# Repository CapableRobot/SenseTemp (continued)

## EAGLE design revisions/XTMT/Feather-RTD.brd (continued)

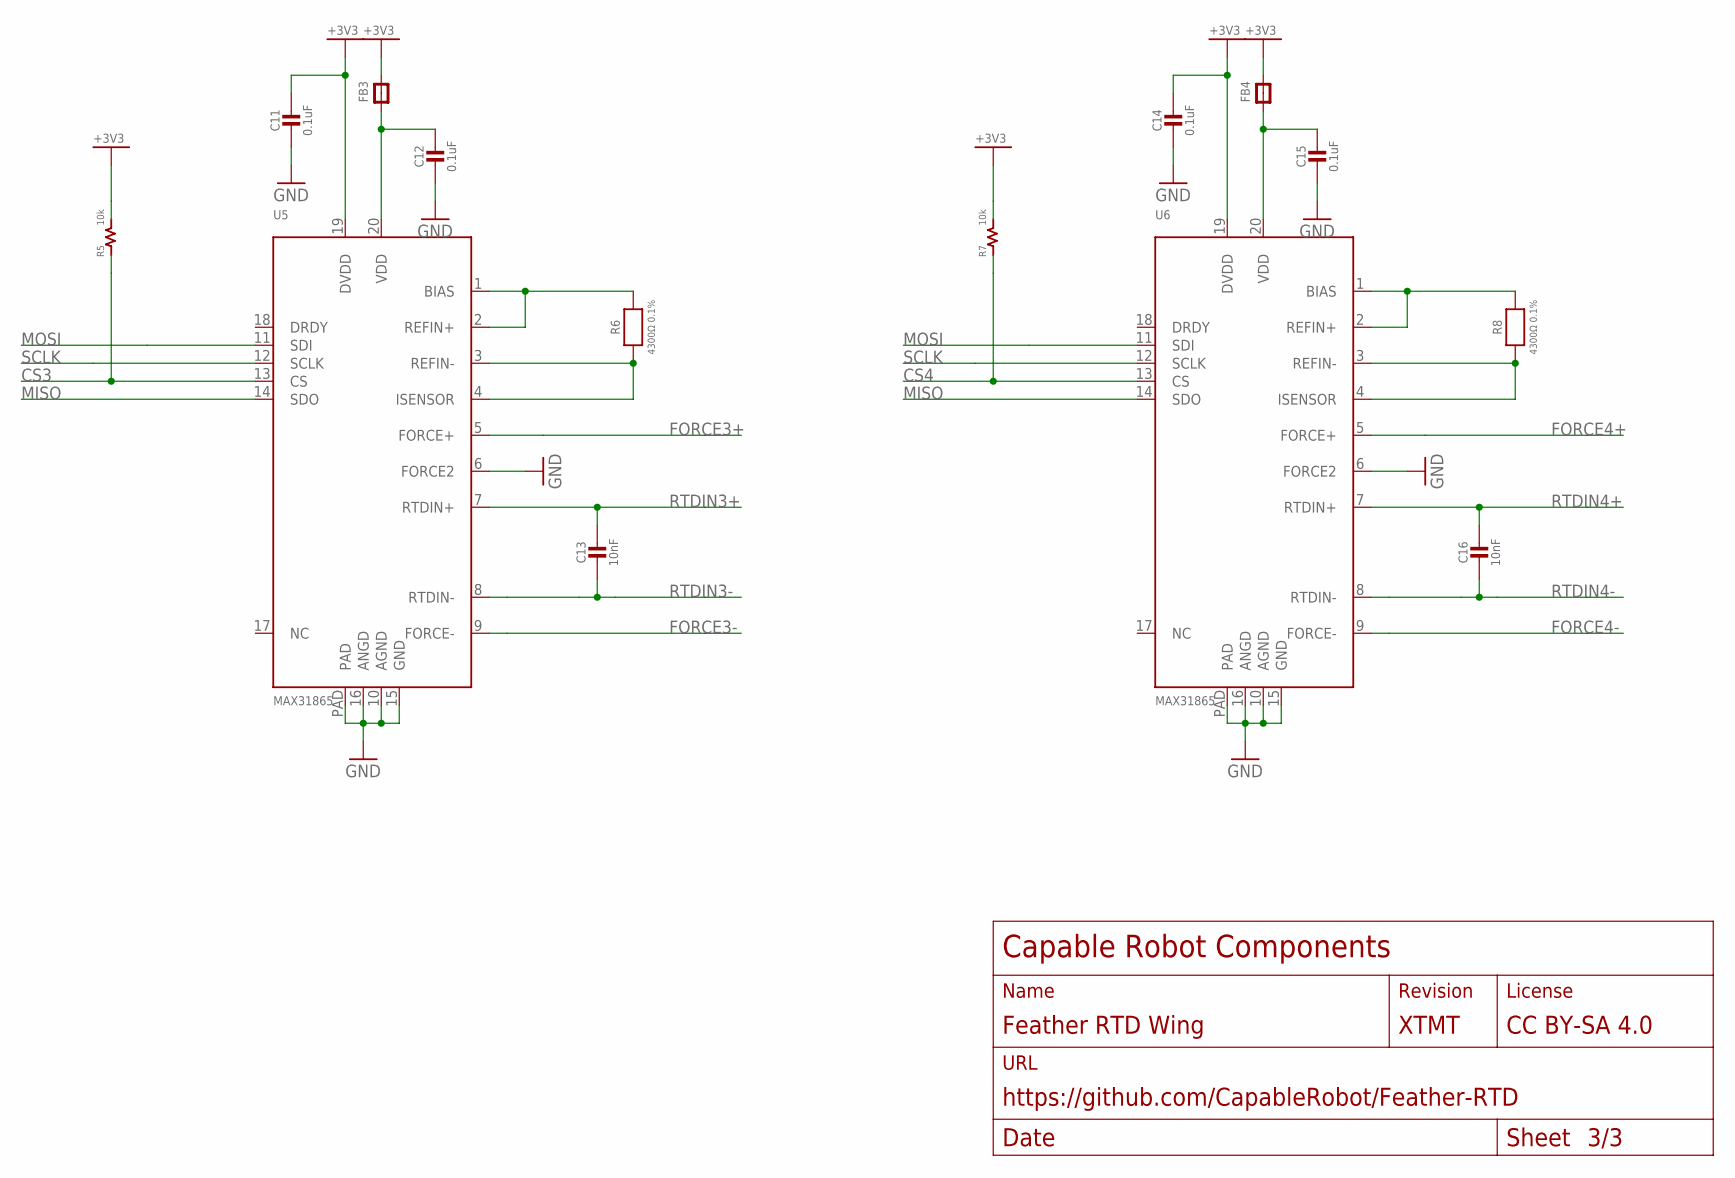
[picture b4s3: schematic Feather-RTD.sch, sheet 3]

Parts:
C11, C12, C14, C15: 0.1uF; 0805-NO
C13, C16: 10nF; 0805-NO
FB3, FB4: FERRITE-0805NO; 0805-NO
R5, R7: 10k; 0603
R6, R8: 4300Ω 0.1%; 0805-NO
U5, U6: MAX31865; QFN20_4MM_0.65MM

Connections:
+3V3: C11.1, C14.1, FB3.2, FB4.2, R5.2, R7.2, U5.19 (DVDD), U6.19 (DVDD); also elsewhere on the board
CS3: R5.1, U5.13 (CS); also elsewhere on the board
CS4: R7.1, U6.13 (CS); also elsewhere on the board
FORCE3+: U5.5 (FORCE+); also elsewhere on the board
FORCE3-: U5.9 (FORCE-); also elsewhere on the board
FORCE4+: U6.5 (FORCE+); also elsewhere on the board
FORCE4-: U6.9 (FORCE-); also elsewhere on the board
GND: C11.2, C12.2, C14.2, C15.2, U5.6 (FORCE2), U5.10 (AGND), U5.15 (GND), U5.16 (ANGD), U5.PAD, U6.6 (FORCE2), U6.10 (AGND), U6.15 (GND), U6.16 (ANGD), U6.PAD; also elsewhere on the board
MISO: U5.14 (SDO), U6.14 (SDO); also elsewhere on the board
MOSI: U5.11 (SDI), U6.11 (SDI); also elsewhere on the board
unnamed: R6.2, U5.1 (BIAS), U5.2 (REFIN+)
unnamed: R6.1, U5.3 (REFIN-), U5.4 (ISENSOR)
unnamed: C12.1, FB3.1, U5.20 (VDD)
unnamed: R8.2, U6.1 (BIAS), U6.2 (REFIN+)
unnamed: R8.1, U6.3 (REFIN-), U6.4 (ISENSOR)
unnamed: C15.1, FB4.1, U6.20 (VDD)
RTDIN3+: C13.1, U5.7 (RTDIN+); also elsewhere on the board
RTDIN3-: C13.2, U5.8 (RTDIN-); also elsewhere on the board
RTDIN4+: C16.1, U6.7 (RTDIN+); also elsewhere on the board
RTDIN4-: C16.2, U6.8 (RTDIN-); also elsewhere on the board
SCLK: U5.12 (SCLK), U6.12 (SCLK); also elsewhere on the board

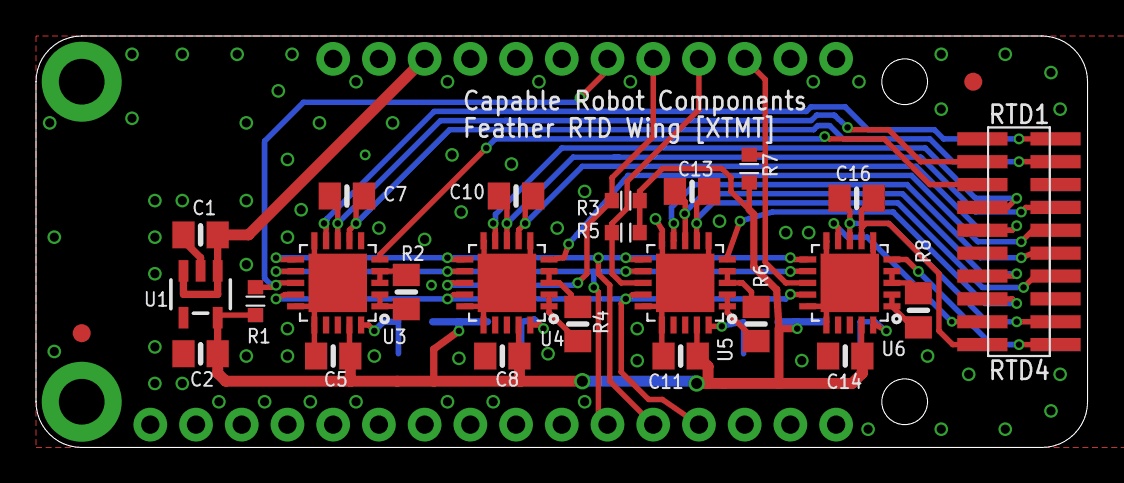
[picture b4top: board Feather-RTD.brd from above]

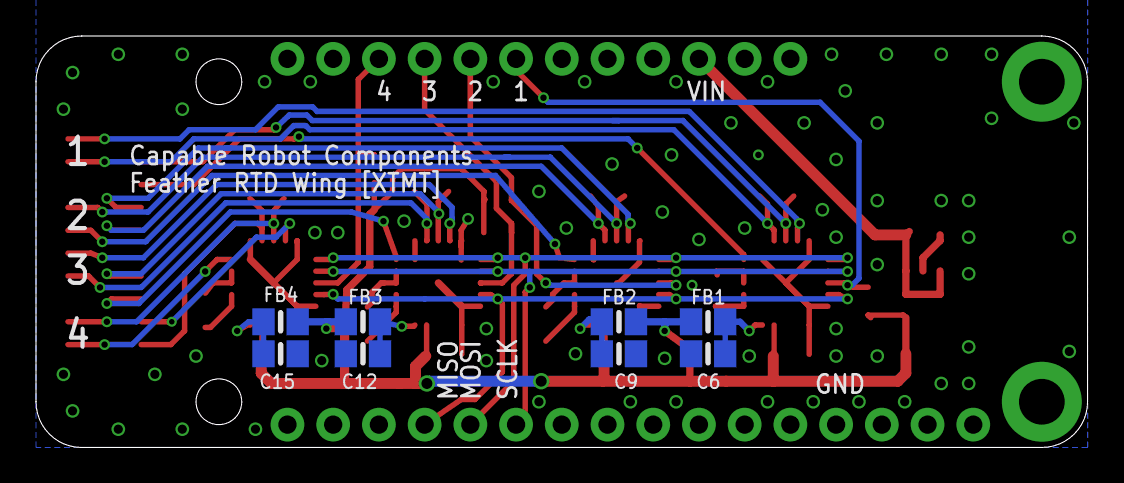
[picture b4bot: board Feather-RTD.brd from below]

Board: 2 copper layers, 58.4 x 22.9 mm, 36 parts (8 on the bottom side), 38 nets.

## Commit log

2018-04-02 Initial commit of software for ESP32 running MicroPython
2018-05-09 Added XTMT hardware design files
2018-05-09 Remove cache files and update ignore file
2018-05-09 Move atributed from page 1 title block to global
2018-05-09 Added generated PDFs from Eagle source files
2018-08-28 Adding X9EG version, out for fab
2018-08-28 Adding PDFs
2018-09-20 Whitespace
2018-09-20 Adding HTTP server
2018-09-20 Adding MicroPython firmware image
2018-09-21 Move libraries to lib folder
2018-09-21 Remove simple HTTP server
2018-09-21 Adding microWebServer
2018-09-21 Fix encoding issue. Change location of some keys in JSON settings. Move to threading model
2018-09-21 Cleanup whitespace
2018-10-17 Added web server demo
2018-10-18 Change name to SenseTemp
2018-10-18 Adding CREAES version - adds user LED and all components on top side
2018-10-18 Adding BOM and json version of X9EG version
2018-10-18 Fix location of REV label
2018-10-18 Added revision history to README. Change license from CC BY-SA 4.0 to CERN OHL v1.2
2018-10-23 Fix issus where sensor data and metadata was publishes on different MQTT topics. Changed to not be a thread.
2018-11-05 Rename software directory
2018-11-05 Added DS_Store to ignore file
2018-11-05 Move micropython content from the main README into one in the micropython folder
2018-11-05 Fix links
2018-11-05 Added better description of SenseTemp
2018-11-08 Adding circuit python code for SenseTemp on the HalloWing
2018-11-08 Added readme to hardware folder. Added note about Li-Ion power source.
2018-11-08 Added image
2018-11-08 Added README with example circuitpython code
2018-11-19 Added OSHW certification
2018-12-04 Added Feather M0/M4 which prints temperature data to the serial console.
2018-12-04 Change color of on-board LED based on RTD1
2018-12-04 Adding neopixel library for M0 / M4 Express demo
2018-12-18 Fix (c) in LICENSE file
2018-12-20 Adding example code for displaying temperature on a OLED screen
2019-01-03 Fix broken link
2019-01-04 Added MicroPython console example
2019-01-04 Change minification method to preseve line breaks
2019-01-04 Added port information to document
2019-01-04 Change formating. Added HTML metatags for better iOS homescreen use. JSON URL no longer hard-coded to default AP-mode address.
2019-01-04 Changed labels in example JSON file
2019-01-23 Added MQTT demo for Adafruit.io service
2019-01-23 Fix calculation issue below 0C
2019-05-10 Adding auto-calibration script
2019-08-13 Change silk screen around RTD connector
2019-10-09 Fix links in readme text
2019-10-09 Added harness drawing
2020-08-28 Adding adapter PCBs to allow connection to 2 wire and 3 wire RTDs
